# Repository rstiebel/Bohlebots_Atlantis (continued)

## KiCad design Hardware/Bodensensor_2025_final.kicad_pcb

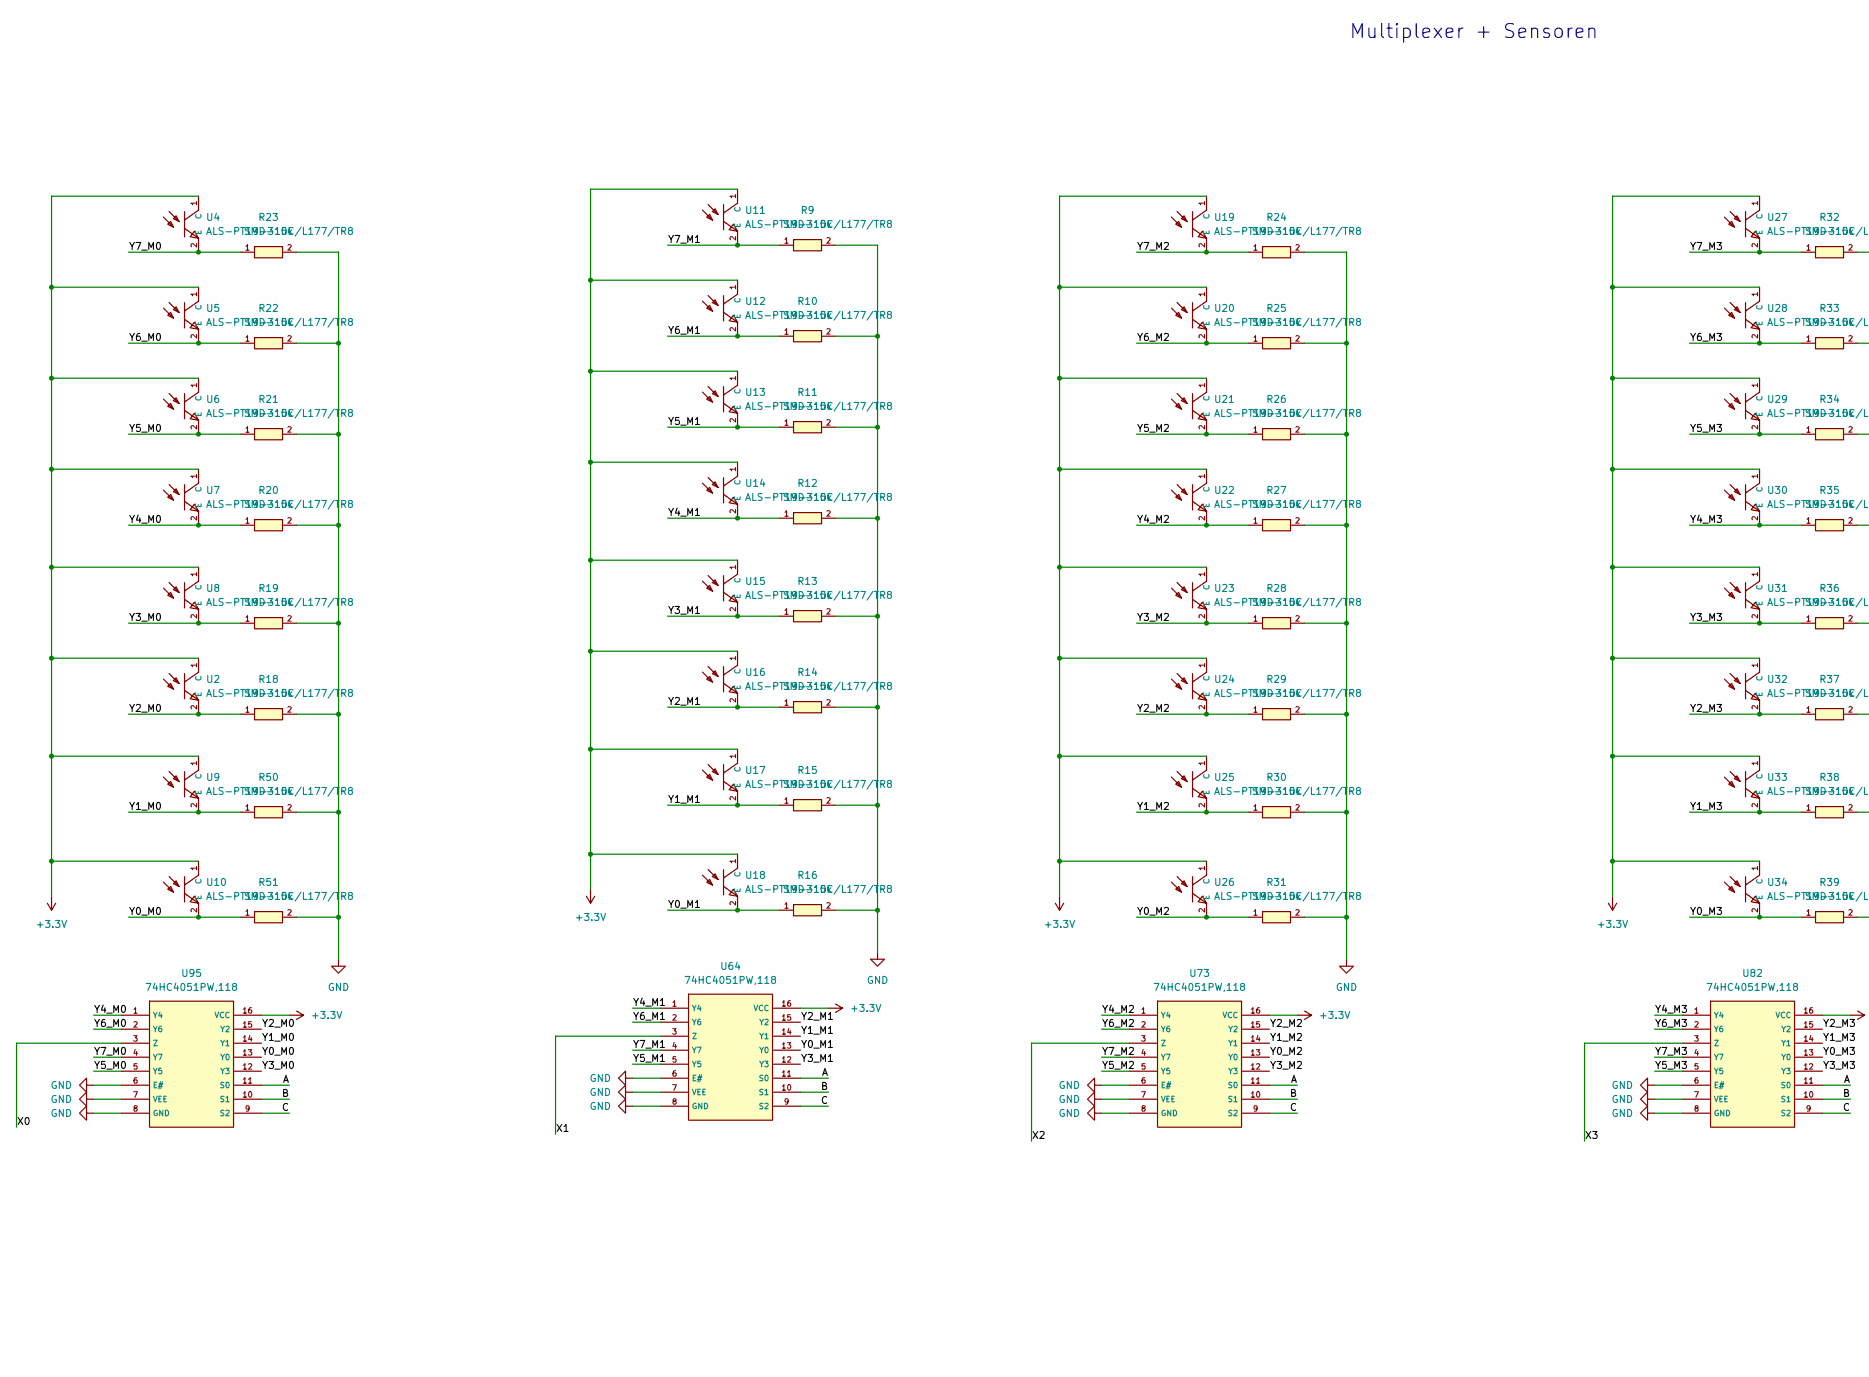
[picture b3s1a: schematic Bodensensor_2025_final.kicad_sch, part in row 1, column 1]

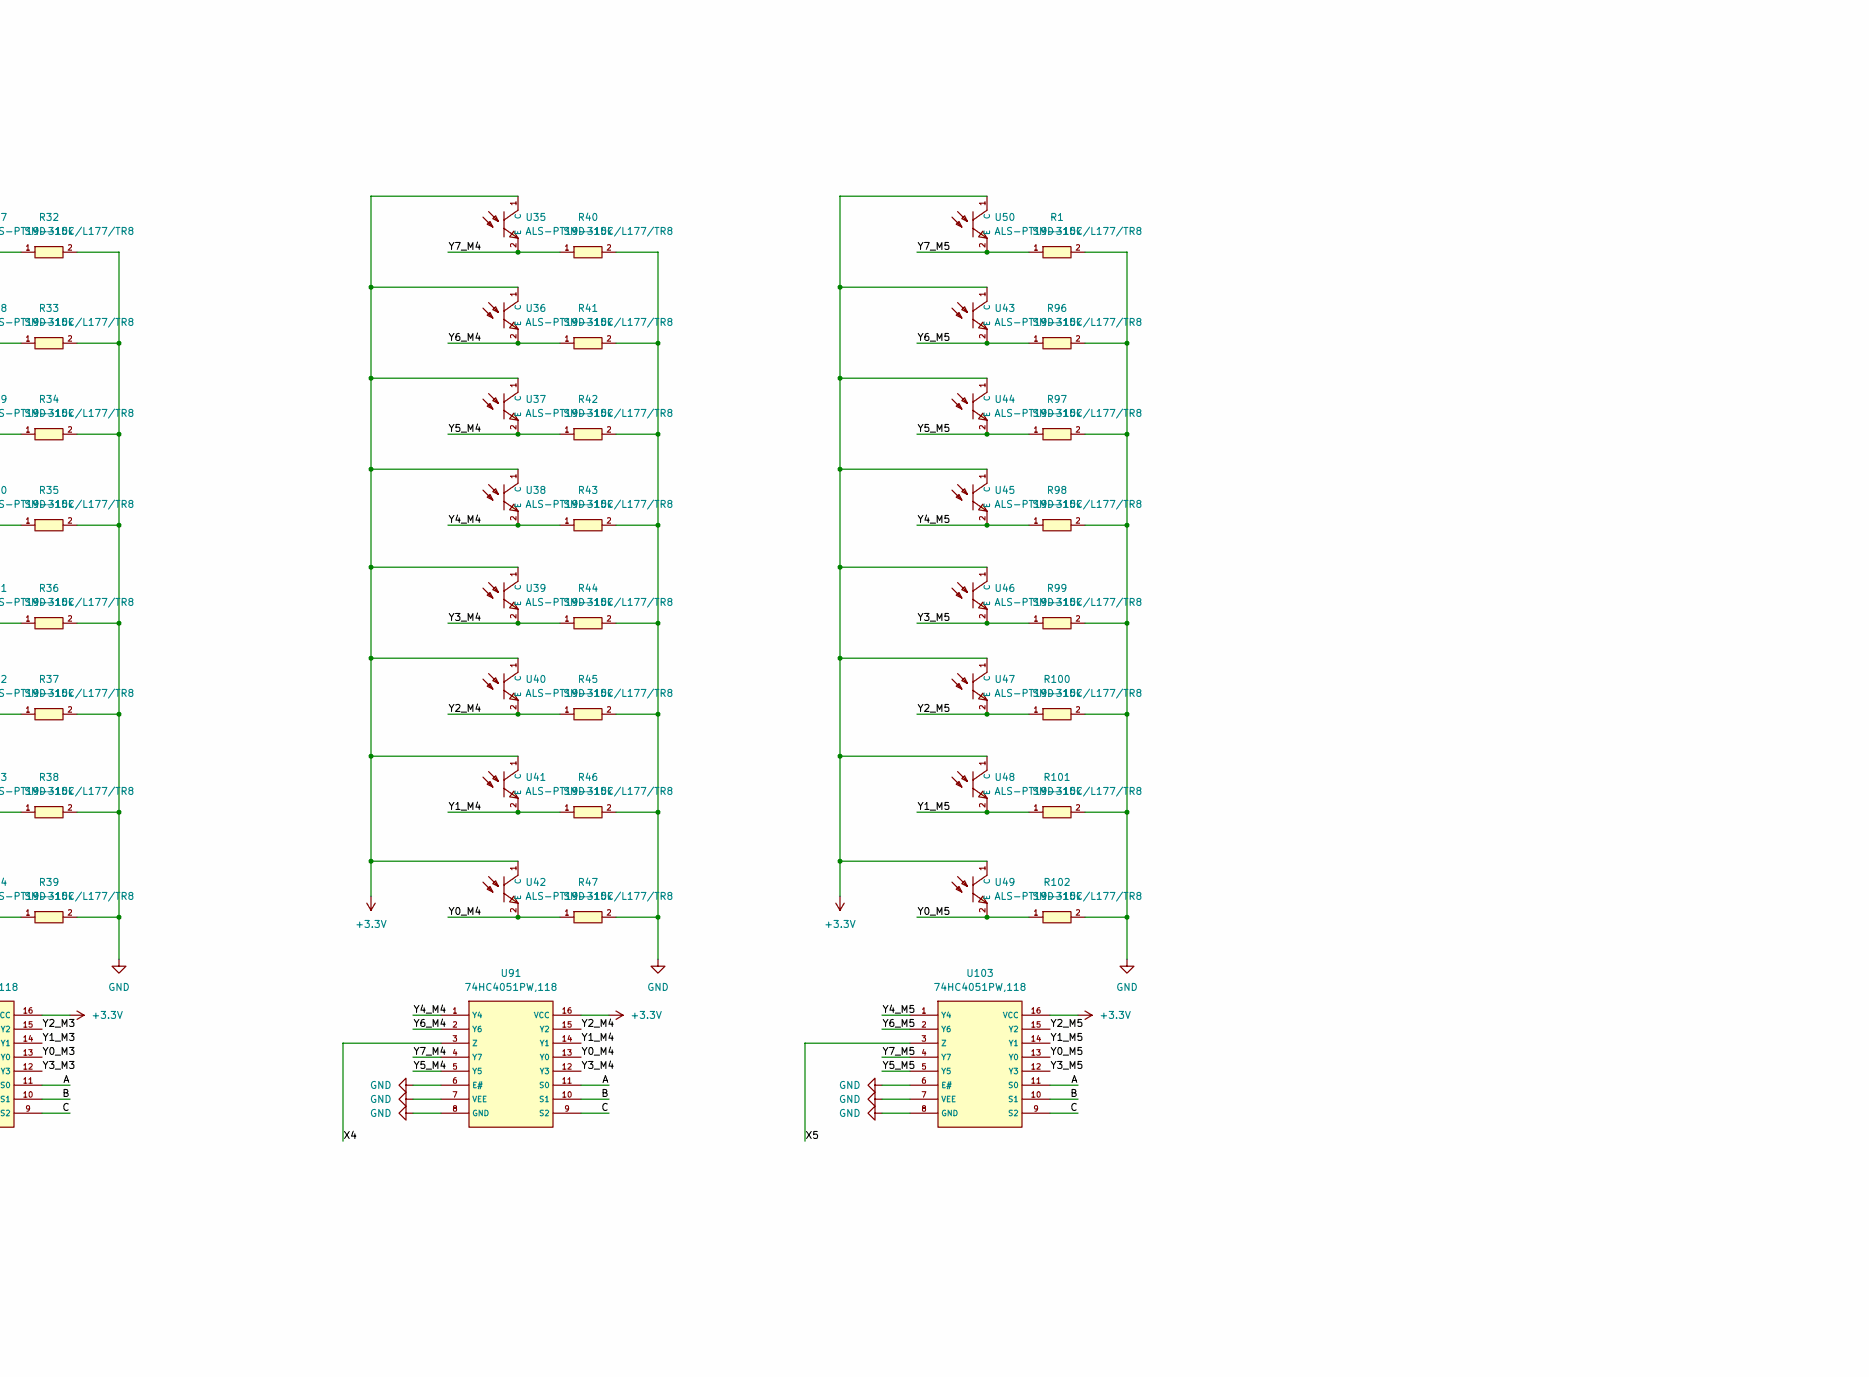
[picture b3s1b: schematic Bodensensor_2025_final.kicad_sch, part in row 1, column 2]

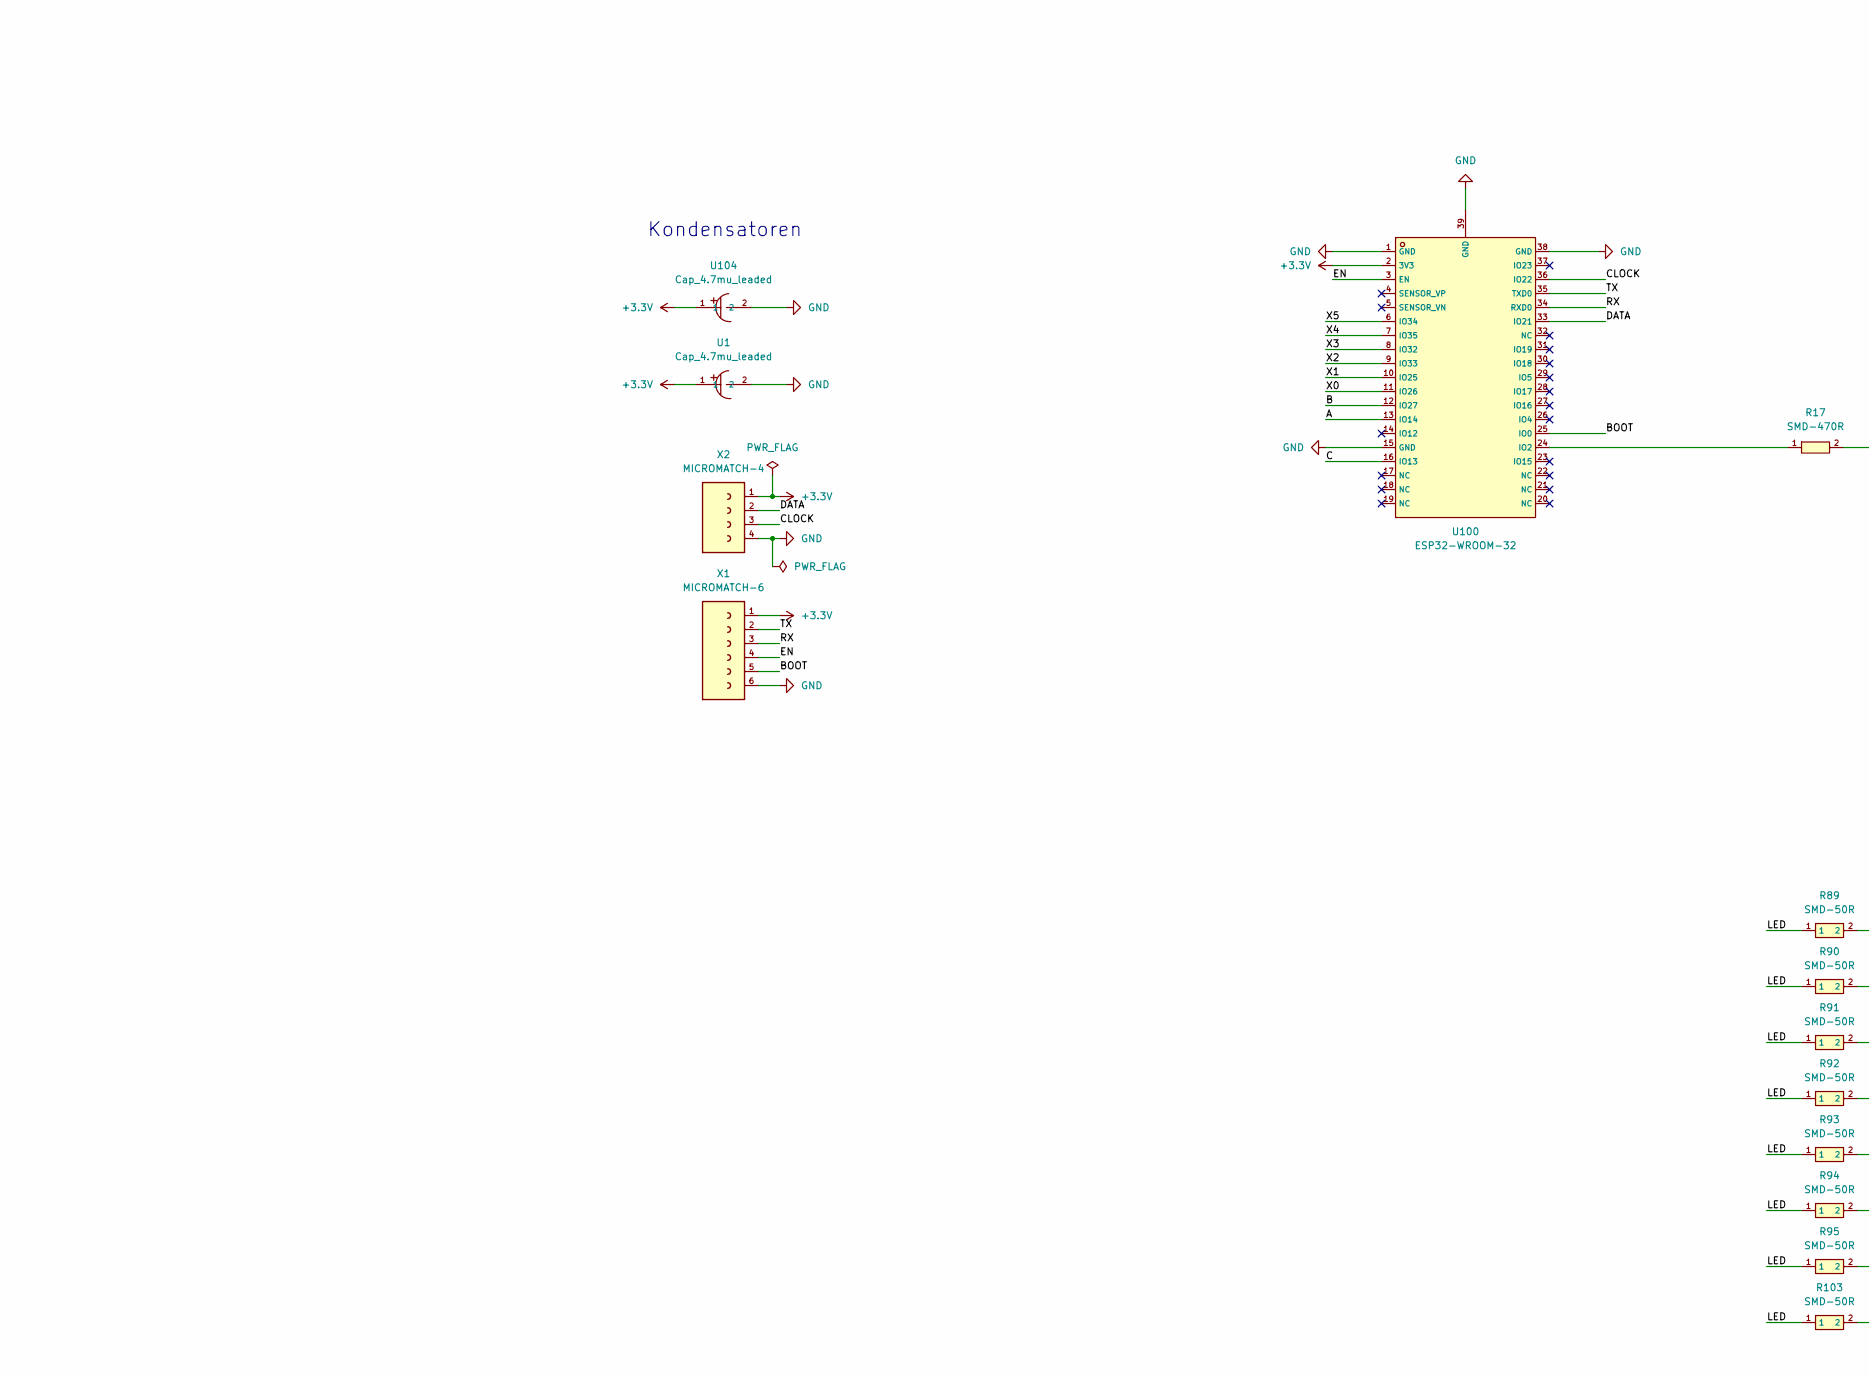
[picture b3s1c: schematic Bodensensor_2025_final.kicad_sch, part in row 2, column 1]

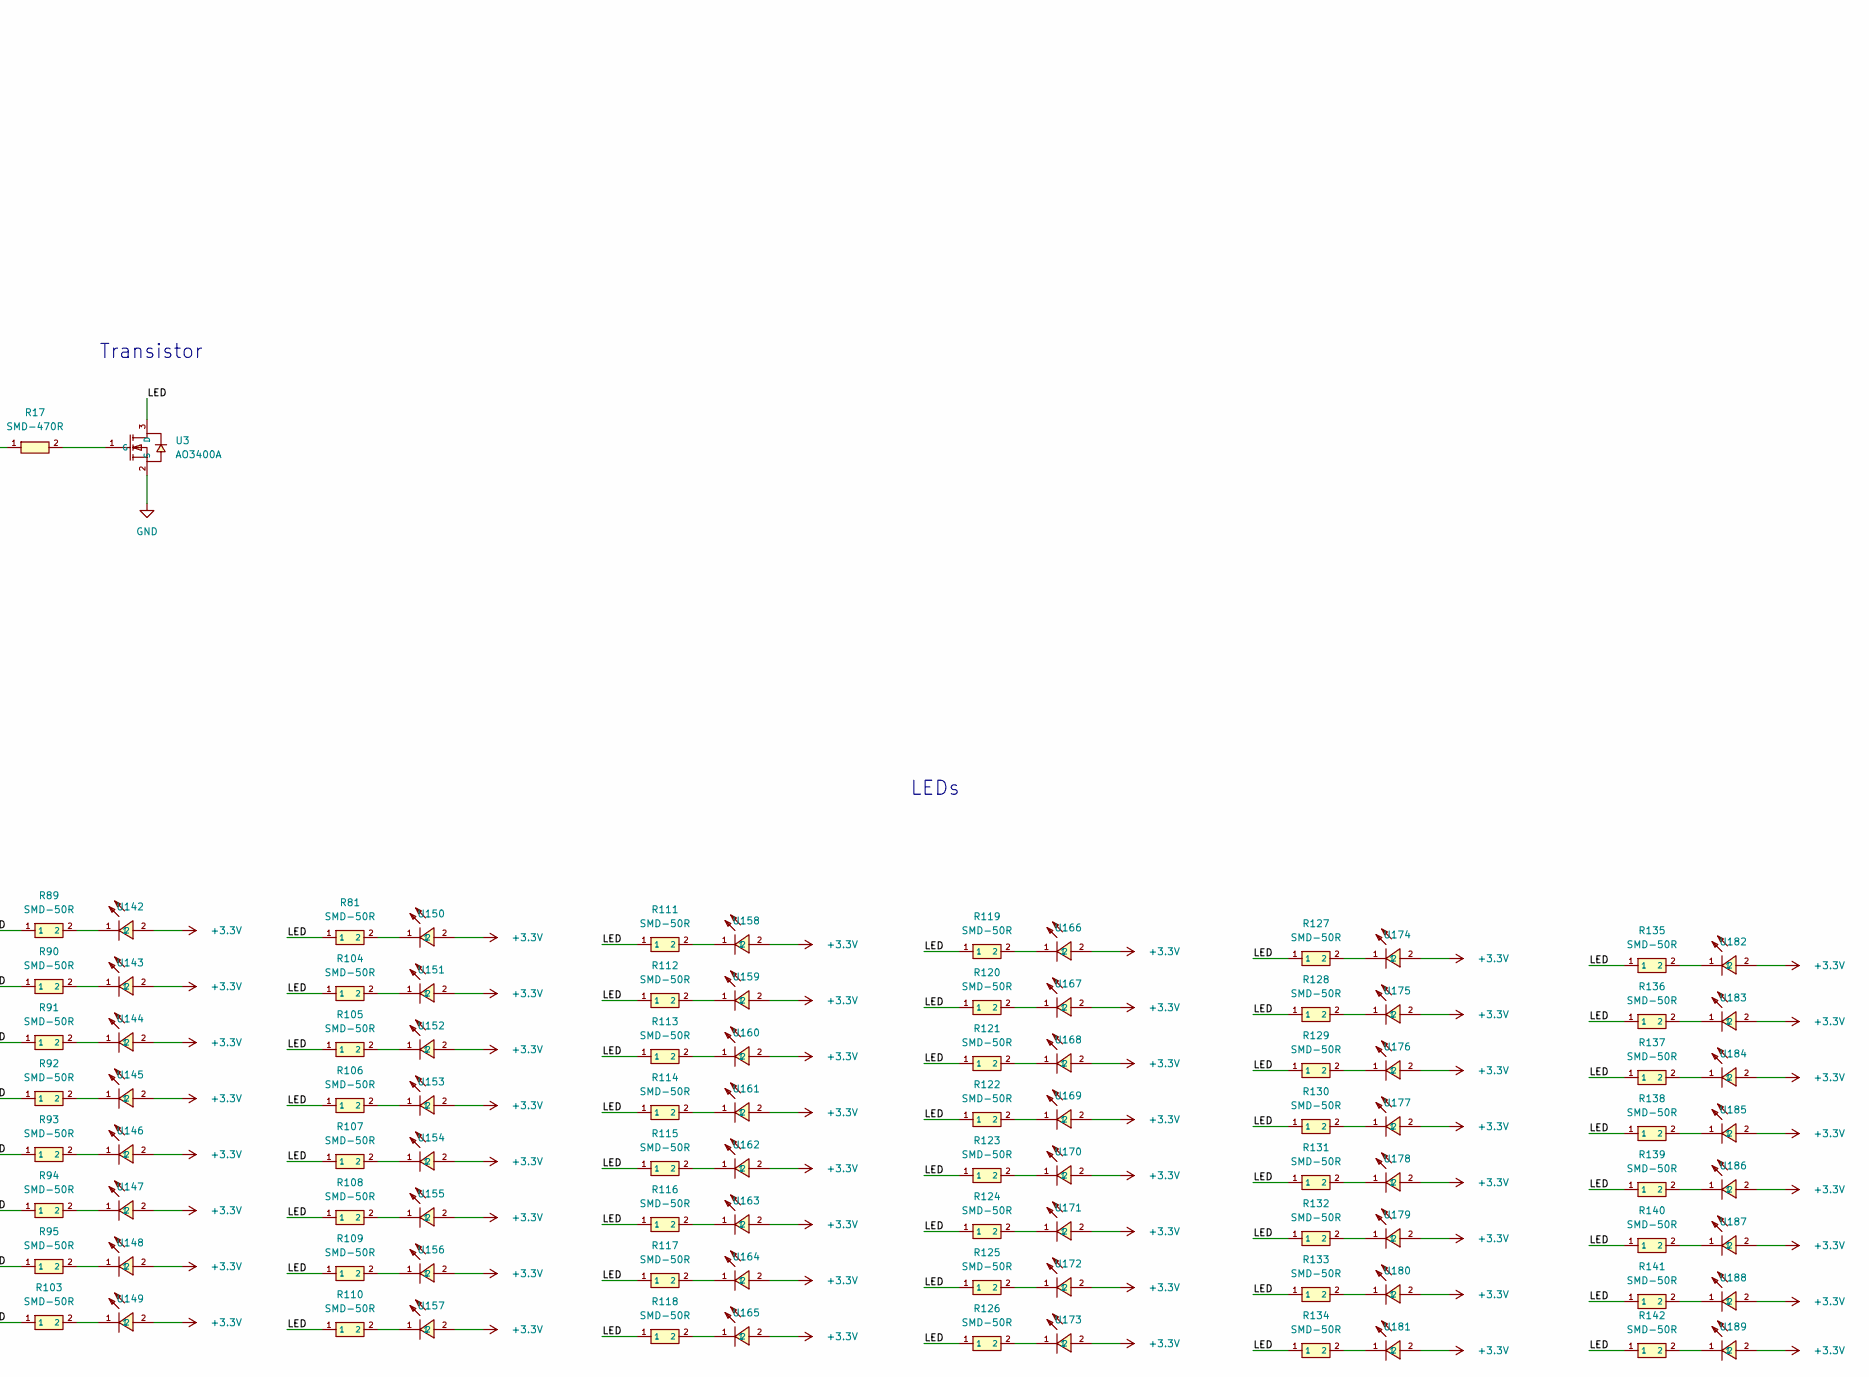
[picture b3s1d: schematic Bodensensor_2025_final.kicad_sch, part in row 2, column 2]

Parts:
R1, R9, R10, R11, R12, R13, R14, R15, R16, R18, R19, R20, R21, R22, R23, R24, R25, R26, R27, R28, R29, R30, R31, R32, R33, R34, R35, R36, R37, R38, R39, R40, R41, R42, R43, R44, R45, R46, R47, R50, R51, R96, R97, R98, R99, R100, R101, R102: SMD-10k; R0603; LCSC C25804
R17: SMD-470R; R0603; LCSC C23162
R81, R89, R90, R91, R92, R93, R94, R95, R103, R104, R105, R106, R107, R108, R109, R110, R111, R112, R113, R114, R115, R116, R117, R118, R119, R120, R121, R122, R123, R124, R125, R126, R127, R128, R129, R130, R131, R132, R133, R134, R135, R136, R137, R138, R139, R140, R141, R142: SMD-50R; R0603; LCSC C849792
U1, U104: Cap_4.7mu_leaded; CAP-TH_BD4.0-P1.50-D0.5-FD; LCSC C2873979
U2, U4, U5, U6, U7, U8, U9, U10, U11, U12, U13, U14, U15, U16, U17, U18, U19, U20, U21, U22, U23, U24, U25, U26, U27, U28, U29, U30, U31, U32, U33, U34, U35, U36, U37, U38, U39, U40, U41, U42, U43, U44, U45, U46, U47, U48, U49, U50: ALS-PT19-315C/L177/TR8; SENSORS-SMD_ALS-PT19; LCSC C146233
U3: AO3400A; SOT-23-3_L2.9-W1.3-P1.90-LS2.4-BR; LCSC C20917
U64, U73, U82, U91, U95, U103: 74HC4051PW,118; TSSOP-16_L5.0-W4.4-P0.65-LS6.4-BL; LCSC C5645
U100: ESP32-WROOM-32; WIFI-SMD_ESP32-WROOM-32UE; LCSC C701344
U142, U143, U144, U145, U146, U147, U148, U149, U150, U151, U152, U153, U154, U155, U156, U157, U158, U159, U160, U161, U162, U163, U164, U165, U166, U167, U168, U169, U170, U171, U172, U173, U174, U175, U176, U177, U178, U179, U180, U181, U182, U183, U184, U185, U186, U187, U188, U189: LED weiß 4000k Bodensensor HL-AM-2835H489W-S1-08H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; LED-SMD_L3.3-W2.8-RD; LCSC C210311
X1: MICROMATCH-6
X2: MICROMATCH-4

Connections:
+3.3V: U1.1, U2.1 (C), U4.1 (C), U5.1 (C), U6.1 (C), U7.1 (C), U8.1 (C), U9.1 (C), U10.1 (C), U11.1 (C), U12.1 (C), U13.1 (C), U14.1 (C), U15.1 (C), U16.1 (C), U17.1 (C), U18.1 (C), U19.1 (C), U20.1 (C), U21.1 (C), U22.1 (C), U23.1 (C), U24.1 (C), U25.1 (C), U26.1 (C), U27.1 (C), U28.1 (C), U29.1 (C), U30.1 (C), U31.1 (C), U32.1 (C), U33.1 (C), U34.1 (C), U35.1 (C), U36.1 (C), U37.1 (C), U38.1 (C), U39.1 (C), U40.1 (C), U41.1 (C), U42.1 (C), U43.1 (C), U44.1 (C), U45.1 (C), U46.1 (C), U47.1 (C), U48.1 (C), U49.1 (C), U50.1 (C), U64.16 (VCC), U73.16 (VCC), U82.16 (VCC), U91.16 (VCC), U95.16 (VCC), U100.2 (3V3), U103.16 (VCC), U104.1, U142.2, U143.2, U144.2, U145.2, U146.2, U147.2, U148.2, U149.2, U150.2, U151.2, U152.2, U153.2, U154.2, U155.2, U156.2, U157.2, U158.2, U159.2, U160.2, U161.2, U162.2, U163.2, U164.2, U165.2, U166.2, U167.2, U168.2, U169.2, U170.2, U171.2, U172.2, U173.2, U174.2, U175.2, U176.2, U177.2, U178.2, U179.2, U180.2, U181.2, U182.2, U183.2, U184.2, U185.2, U186.2, U187.2, U188.2, U189.2, X1.1, X2.1
/A: U64.11 (S0), U73.11 (S0), U82.11 (S0), U91.11 (S0), U95.11 (S0), U100.13 (IO14), U103.11 (S0)
/B: U64.10 (S1), U73.10 (S1), U82.10 (S1), U91.10 (S1), U95.10 (S1), U100.12 (IO27), U103.10 (S1)
/BOOT: U100.25 (IO0), X1.5
/C: U64.9 (S2), U73.9 (S2), U82.9 (S2), U91.9 (S2), U95.9 (S2), U100.16 (IO13), U103.9 (S2)
/CLOCK: U100.36 (IO22), X2.3
/DATA: U100.33 (IO21), X2.2
/EN: U100.3 (EN), X1.4
/LED: R81.1, R89.1, R90.1, R91.1, R92.1, R93.1, R94.1, R95.1, R103.1, R104.1, R105.1, R106.1, R107.1, R108.1, R109.1, R110.1, R111.1, R112.1, R113.1, R114.1, R115.1, R116.1, R117.1, R118.1, R119.1, R120.1, R121.1, R122.1, R123.1, R124.1, R125.1, R126.1, R127.1, R128.1, R129.1, R130.1, R131.1, R132.1, R133.1, R134.1, R135.1, R136.1, R137.1, R138.1, R139.1, R140.1, R141.1, R142.1, U3.3 (D)
/RX: U100.34 (RXD0), X1.3
/TX: U100.35 (TXD0), X1.2
/X0: U95.3 (Z), U100.11 (IO26)
/X1: U64.3 (Z), U100.10 (IO25)
/X2: U73.3 (Z), U100.9 (IO33)
/X3: U82.3 (Z), U100.8 (IO32)
/X4: U91.3 (Z), U100.7 (IO35)
/X5: U100.6 (IO34), U103.3 (Z)
/Y0_M0: R51.1, U10.2 (E), U95.13 (Y0)
/Y0_M1: R16.1, U18.2 (E), U64.13 (Y0)
/Y0_M2: R31.1, U26.2 (E), U73.13 (Y0)
/Y0_M3: R39.1, U34.2 (E), U82.13 (Y0)
/Y0_M4: R47.1, U42.2 (E), U91.13 (Y0)
/Y0_M5: R102.1, U49.2 (E), U103.13 (Y0)
/Y1_M0: R50.1, U9.2 (E), U95.14 (Y1)
/Y1_M1: R15.1, U17.2 (E), U64.14 (Y1)
/Y1_M2: R30.1, U25.2 (E), U73.14 (Y1)
/Y1_M3: R38.1, U33.2 (E), U82.14 (Y1)
/Y1_M4: R46.1, U41.2 (E), U91.14 (Y1)
/Y1_M5: R101.1, U48.2 (E), U103.14 (Y1)
/Y2_M0: R18.1, U2.2 (E), U95.15 (Y2)
/Y2_M1: R14.1, U16.2 (E), U64.15 (Y2)
/Y2_M2: R29.1, U24.2 (E), U73.15 (Y2)
/Y2_M3: R37.1, U32.2 (E), U82.15 (Y2)
/Y2_M4: R45.1, U40.2 (E), U91.15 (Y2)
/Y2_M5: R100.1, U47.2 (E), U103.15 (Y2)
/Y3_M0: R19.1, U8.2 (E), U95.12 (Y3)
/Y3_M1: R13.1, U15.2 (E), U64.12 (Y3)
/Y3_M2: R28.1, U23.2 (E), U73.12 (Y3)
/Y3_M3: R36.1, U31.2 (E), U82.12 (Y3)
/Y3_M4: R44.1, U39.2 (E), U91.12 (Y3)
/Y3_M5: R99.1, U46.2 (E), U103.12 (Y3)
/Y4_M0: R20.1, U7.2 (E), U95.1 (Y4)
/Y4_M1: R12.1, U14.2 (E), U64.1 (Y4)
/Y4_M2: R27.1, U22.2 (E), U73.1 (Y4)
/Y4_M3: R35.1, U30.2 (E), U82.1 (Y4)
/Y4_M4: R43.1, U38.2 (E), U91.1 (Y4)
/Y4_M5: R98.1, U45.2 (E), U103.1 (Y4)
/Y5_M0: R21.1, U6.2 (E), U95.5 (Y5)
/Y5_M1: R11.1, U13.2 (E), U64.5 (Y5)
/Y5_M2: R26.1, U21.2 (E), U73.5 (Y5)
/Y5_M3: R34.1, U29.2 (E), U82.5 (Y5)
/Y5_M4: R42.1, U37.2 (E), U91.5 (Y5)
/Y5_M5: R97.1, U44.2 (E), U103.5 (Y5)
/Y6_M0: R22.1, U5.2 (E), U95.2 (Y6)
/Y6_M1: R10.1, U12.2 (E), U64.2 (Y6)
/Y6_M2: R25.1, U20.2 (E), U73.2 (Y6)
/Y6_M3: R33.1, U28.2 (E), U82.2 (Y6)
/Y6_M4: R41.1, U36.2 (E), U91.2 (Y6)
/Y6_M5: R96.1, U43.2 (E), U103.2 (Y6)
/Y7_M0: R23.1, U4.2 (E), U95.4 (Y7)
/Y7_M1: R9.1, U11.2 (E), U64.4 (Y7)
/Y7_M2: R24.1, U19.2 (E), U73.4 (Y7)
/Y7_M3: R32.1, U27.2 (E), U82.4 (Y7)
/Y7_M4: R40.1, U35.2 (E), U91.4 (Y7)
/Y7_M5: R1.1, U50.2 (E), U103.4 (Y7)
GND: R1.2, R9.2, R10.2, R11.2, R12.2, R13.2, R14.2, R15.2, R16.2, R18.2, R19.2, R20.2, R21.2, R22.2, R23.2, R24.2, R25.2, R26.2, R27.2, R28.2, R29.2, R30.2, R31.2, R32.2, R33.2, R34.2, R35.2, R36.2, R37.2, R38.2, R39.2, R40.2, R41.2, R42.2, R43.2, R44.2, R45.2, R46.2, R47.2, R50.2, R51.2, R96.2, R97.2, R98.2, R99.2, R100.2, R101.2, R102.2, U1.2, U3.2 (S), U64.6 (E#), U64.7 (VEE), U64.8 (GND), U73.6 (E#), U73.7 (VEE), U73.8 (GND), U82.6 (E#), U82.7 (VEE), U82.8 (GND), U91.6 (E#), U91.7 (VEE), U91.8 (GND), U95.6 (E#), U95.7 (VEE), U95.8 (GND), U100.1 (GND), U100.15 (GND), U100.38 (GND), U100.39 (GND), U103.6 (E#), U103.7 (VEE), U103.8 (GND), U104.2, X1.6, X2.4
unnamed: R81.2, U150.1
unnamed: R89.2, U142.1
unnamed: R90.2, U143.1
unnamed: R91.2, U144.1
unnamed: R92.2, U145.1
unnamed: R93.2, U146.1
unnamed: R94.2, U147.1
unnamed: R95.2, U148.1
unnamed: R103.2, U149.1
unnamed: R104.2, U151.1
unnamed: R105.2, U152.1
unnamed: R106.2, U153.1
unnamed: R107.2, U154.1
unnamed: R108.2, U155.1
unnamed: R109.2, U156.1
unnamed: R110.2, U157.1
unnamed: R111.2, U158.1
unnamed: R112.2, U159.1
unnamed: R113.2, U160.1
unnamed: R114.2, U161.1
unnamed: R115.2, U162.1
unnamed: R116.2, U163.1
unnamed: R117.2, U164.1
unnamed: R118.2, U165.1
unnamed: R119.2, U166.1
unnamed: R120.2, U167.1
unnamed: R121.2, U168.1
unnamed: R122.2, U169.1
unnamed: R123.2, U170.1
unnamed: R124.2, U171.1
unnamed: R125.2, U172.1
unnamed: R126.2, U173.1
unnamed: R127.2, U174.1
unnamed: R128.2, U175.1
unnamed: R129.2, U176.1
unnamed: R130.2, U177.1
unnamed: R131.2, U178.1
unnamed: R132.2, U179.1
unnamed: R133.2, U180.1
unnamed: R134.2, U181.1
unnamed: R135.2, U182.1
unnamed: R136.2, U183.1
unnamed: R137.2, U184.1
unnamed: R138.2, U185.1
unnamed: R139.2, U186.1
unnamed: R140.2, U187.1
unnamed: R141.2, U188.1
unnamed: R142.2, U189.1
unnamed: R17.2, U3.1 (G)
unnamed: R17.1, U100.24 (IO2)

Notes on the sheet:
Kondensatoren
Transistor
Multiplexer + Sensoren
LEDs

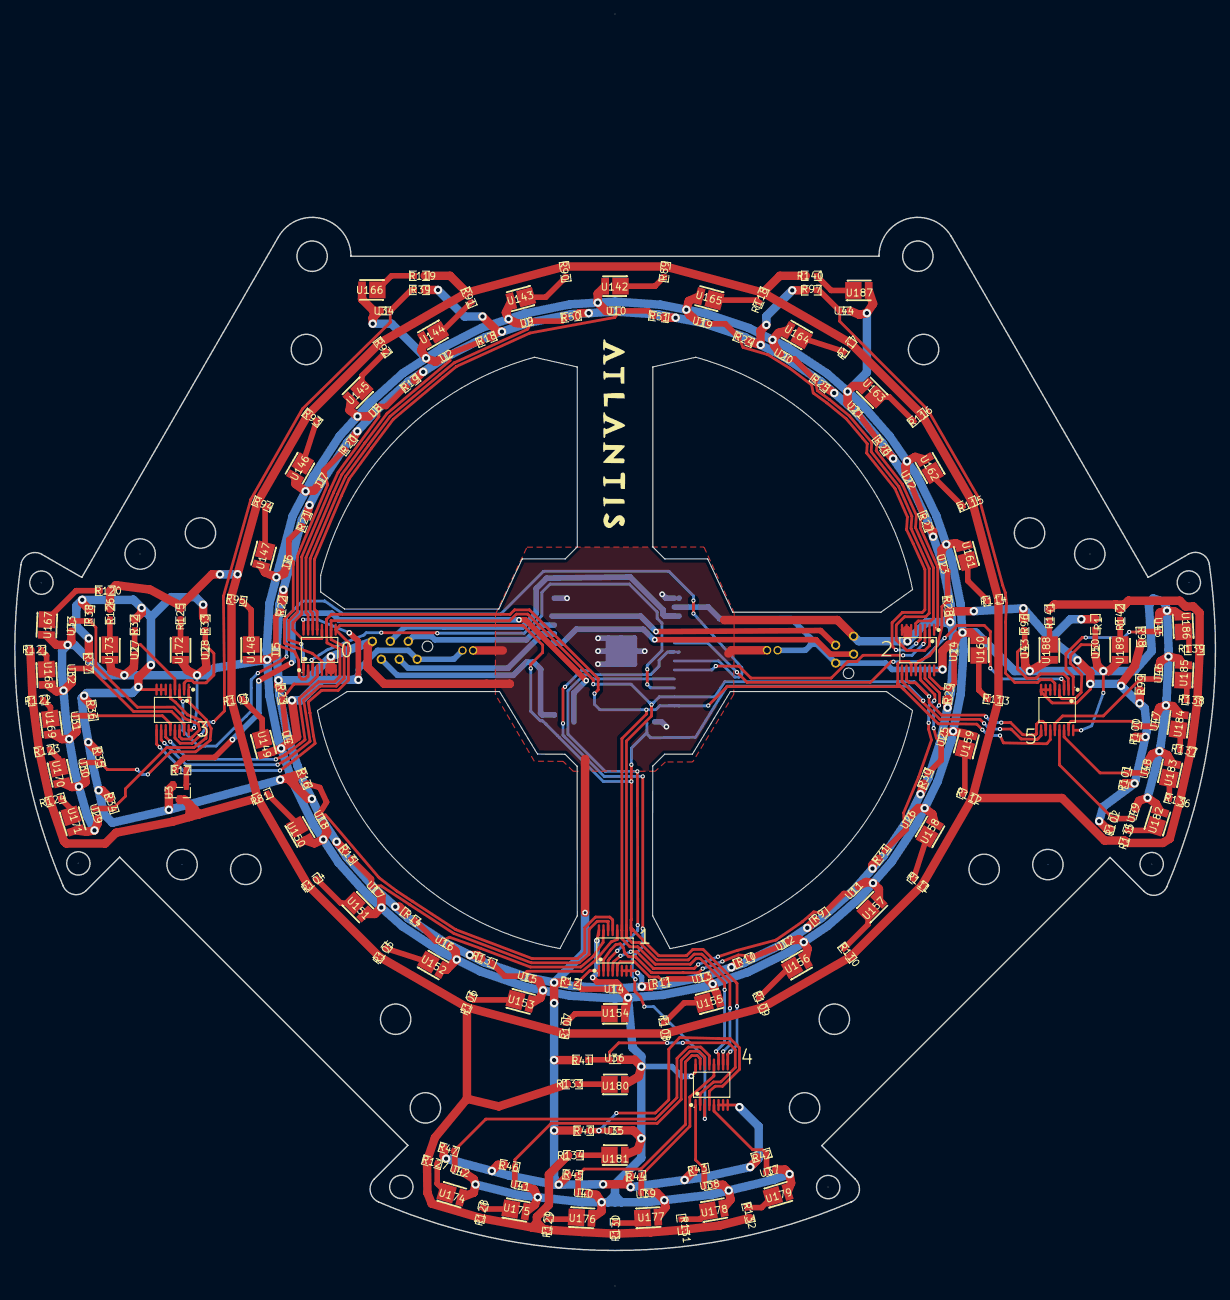
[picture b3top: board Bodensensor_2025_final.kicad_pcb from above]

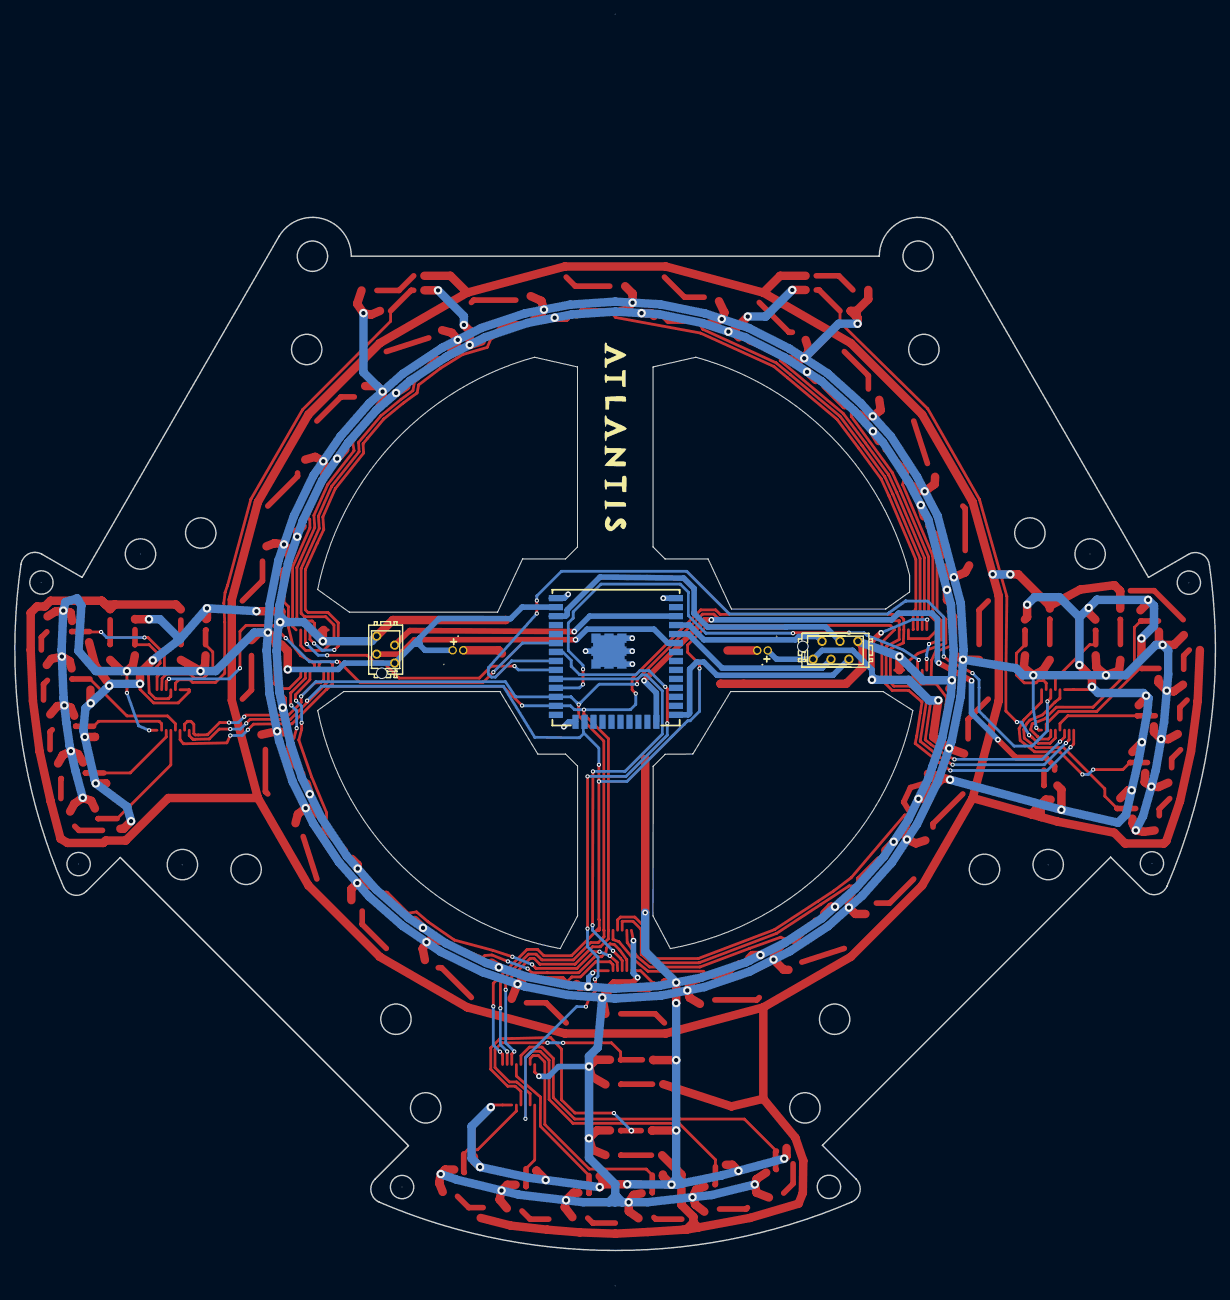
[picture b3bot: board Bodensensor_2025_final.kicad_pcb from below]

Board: 2 copper layers, 170.0 x 146.2 mm, 205 parts (5 on the bottom side), 116 nets.

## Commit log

2026-06-28 Removed test file
2026-06-28 Added Vision system
2026-06-28 Added fusion file
2026-06-28 Added arduino files
2026-06-28 Add PCB and SCH
